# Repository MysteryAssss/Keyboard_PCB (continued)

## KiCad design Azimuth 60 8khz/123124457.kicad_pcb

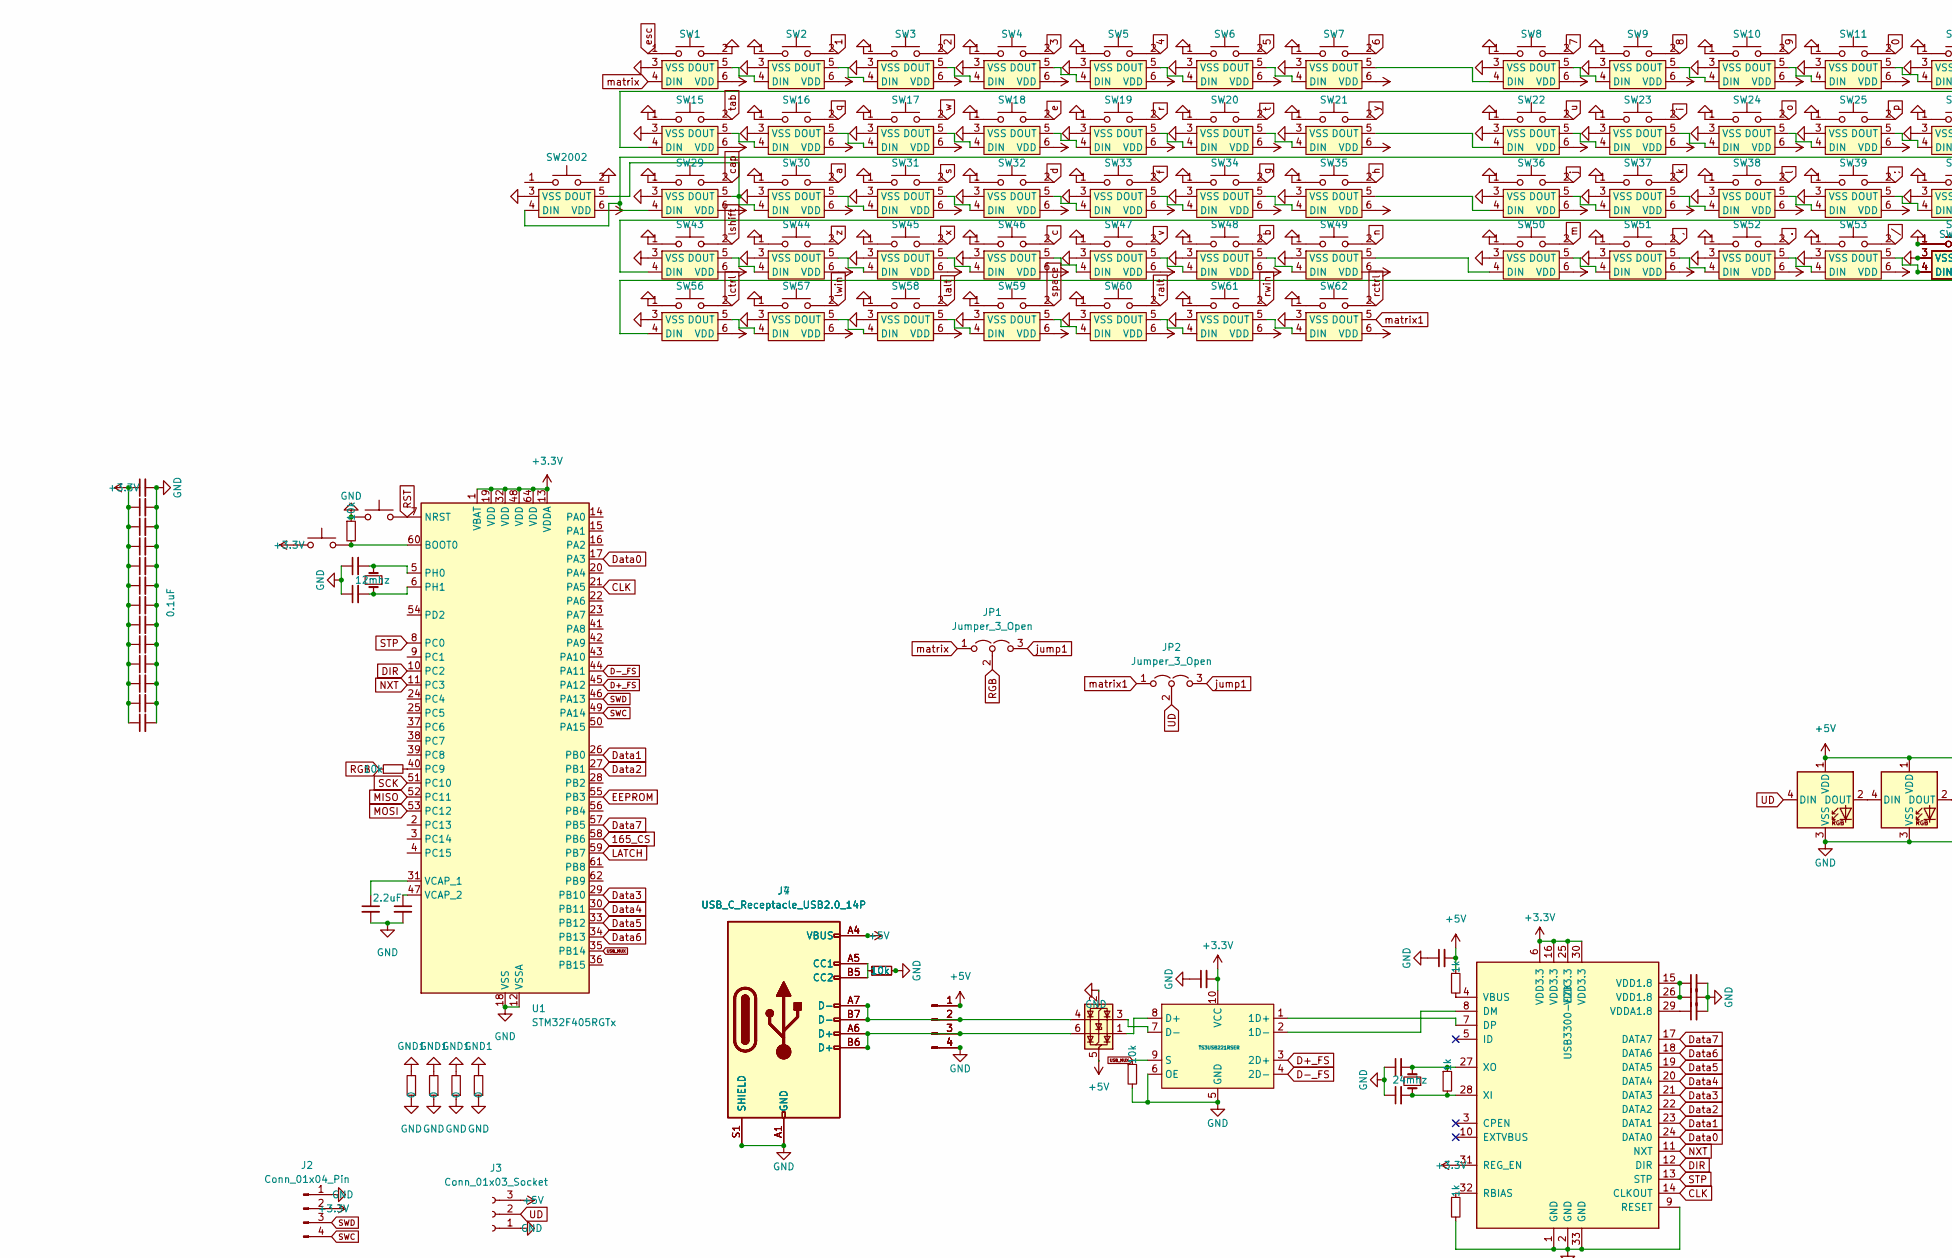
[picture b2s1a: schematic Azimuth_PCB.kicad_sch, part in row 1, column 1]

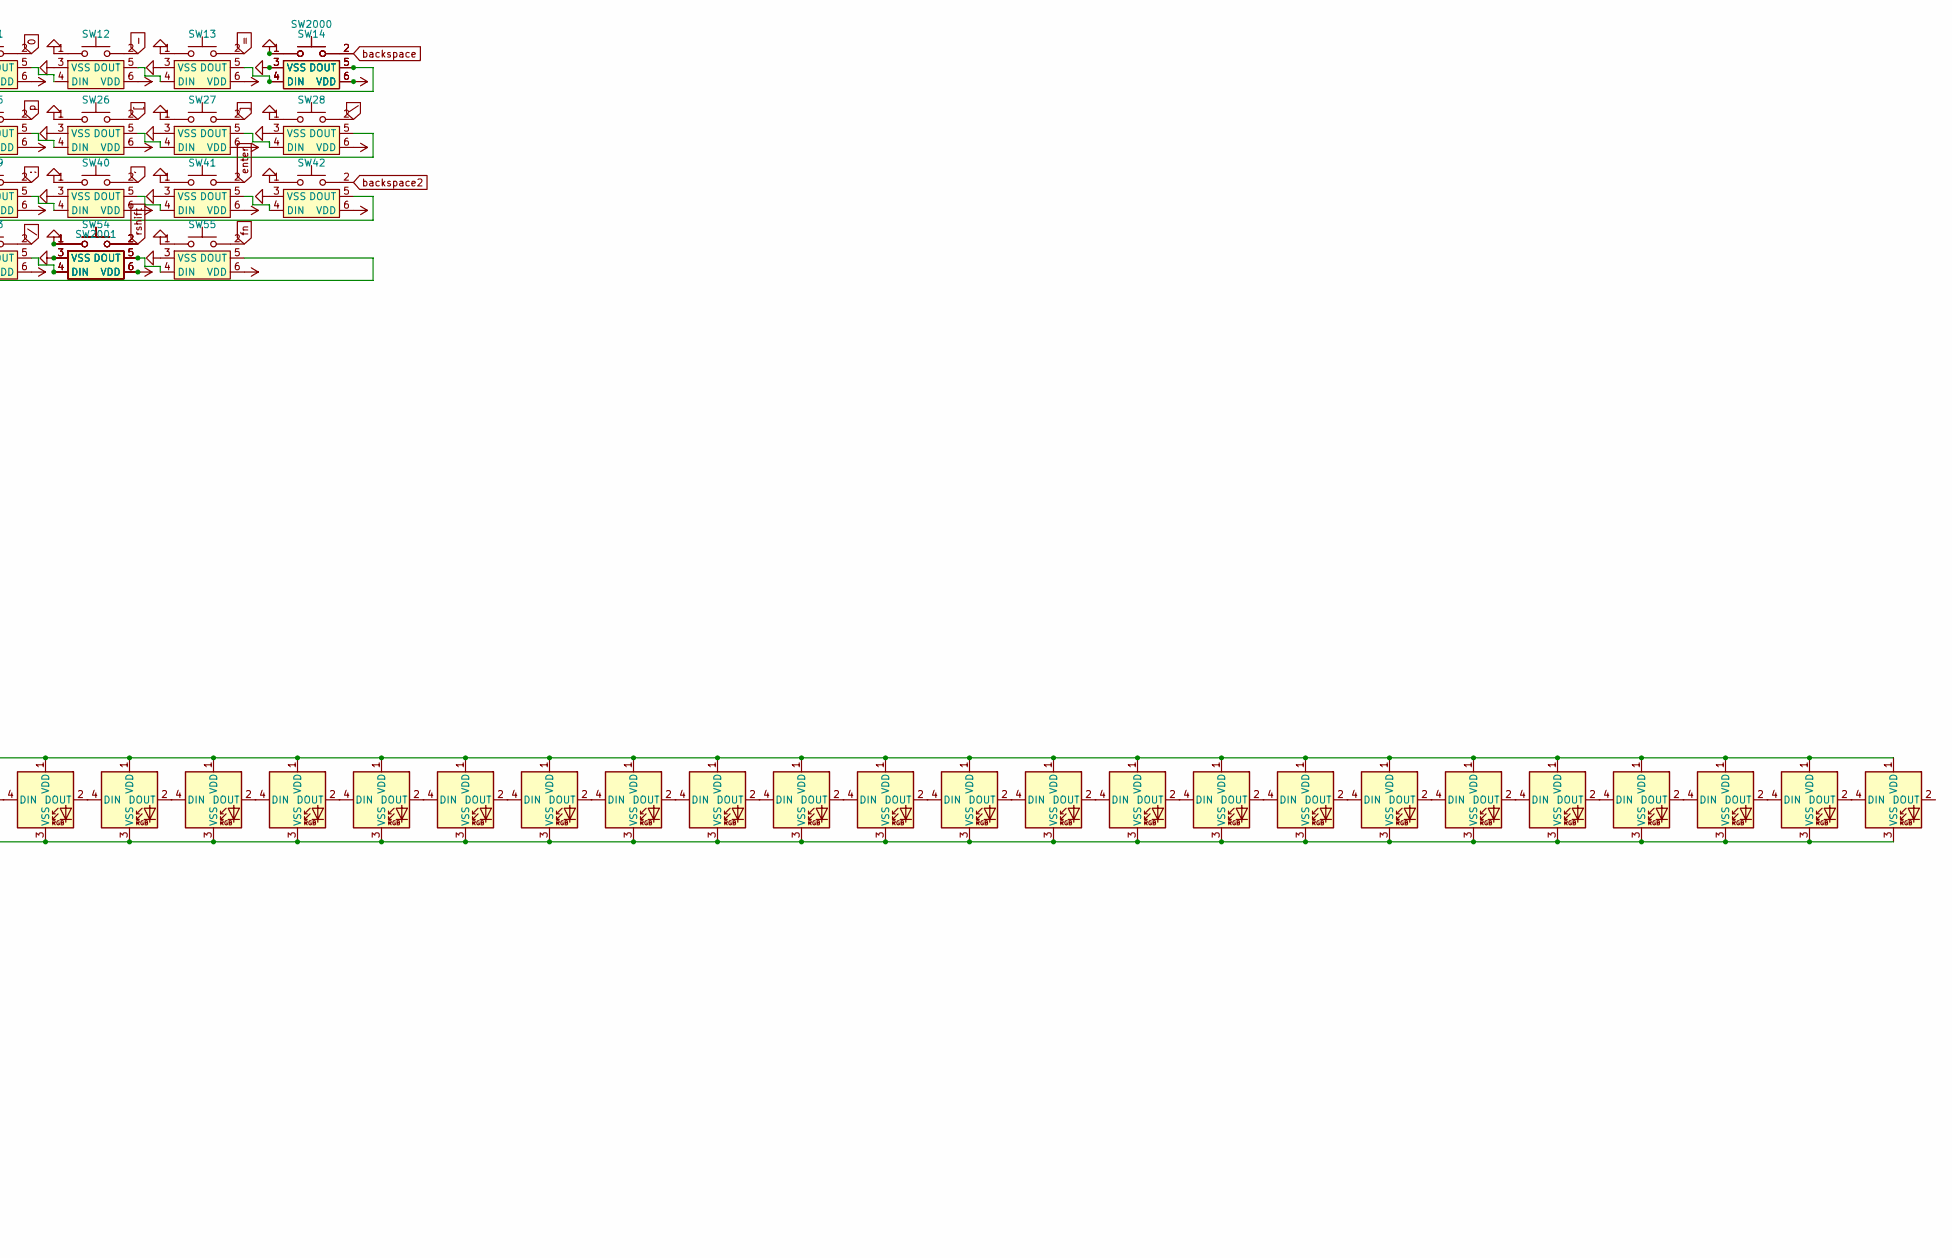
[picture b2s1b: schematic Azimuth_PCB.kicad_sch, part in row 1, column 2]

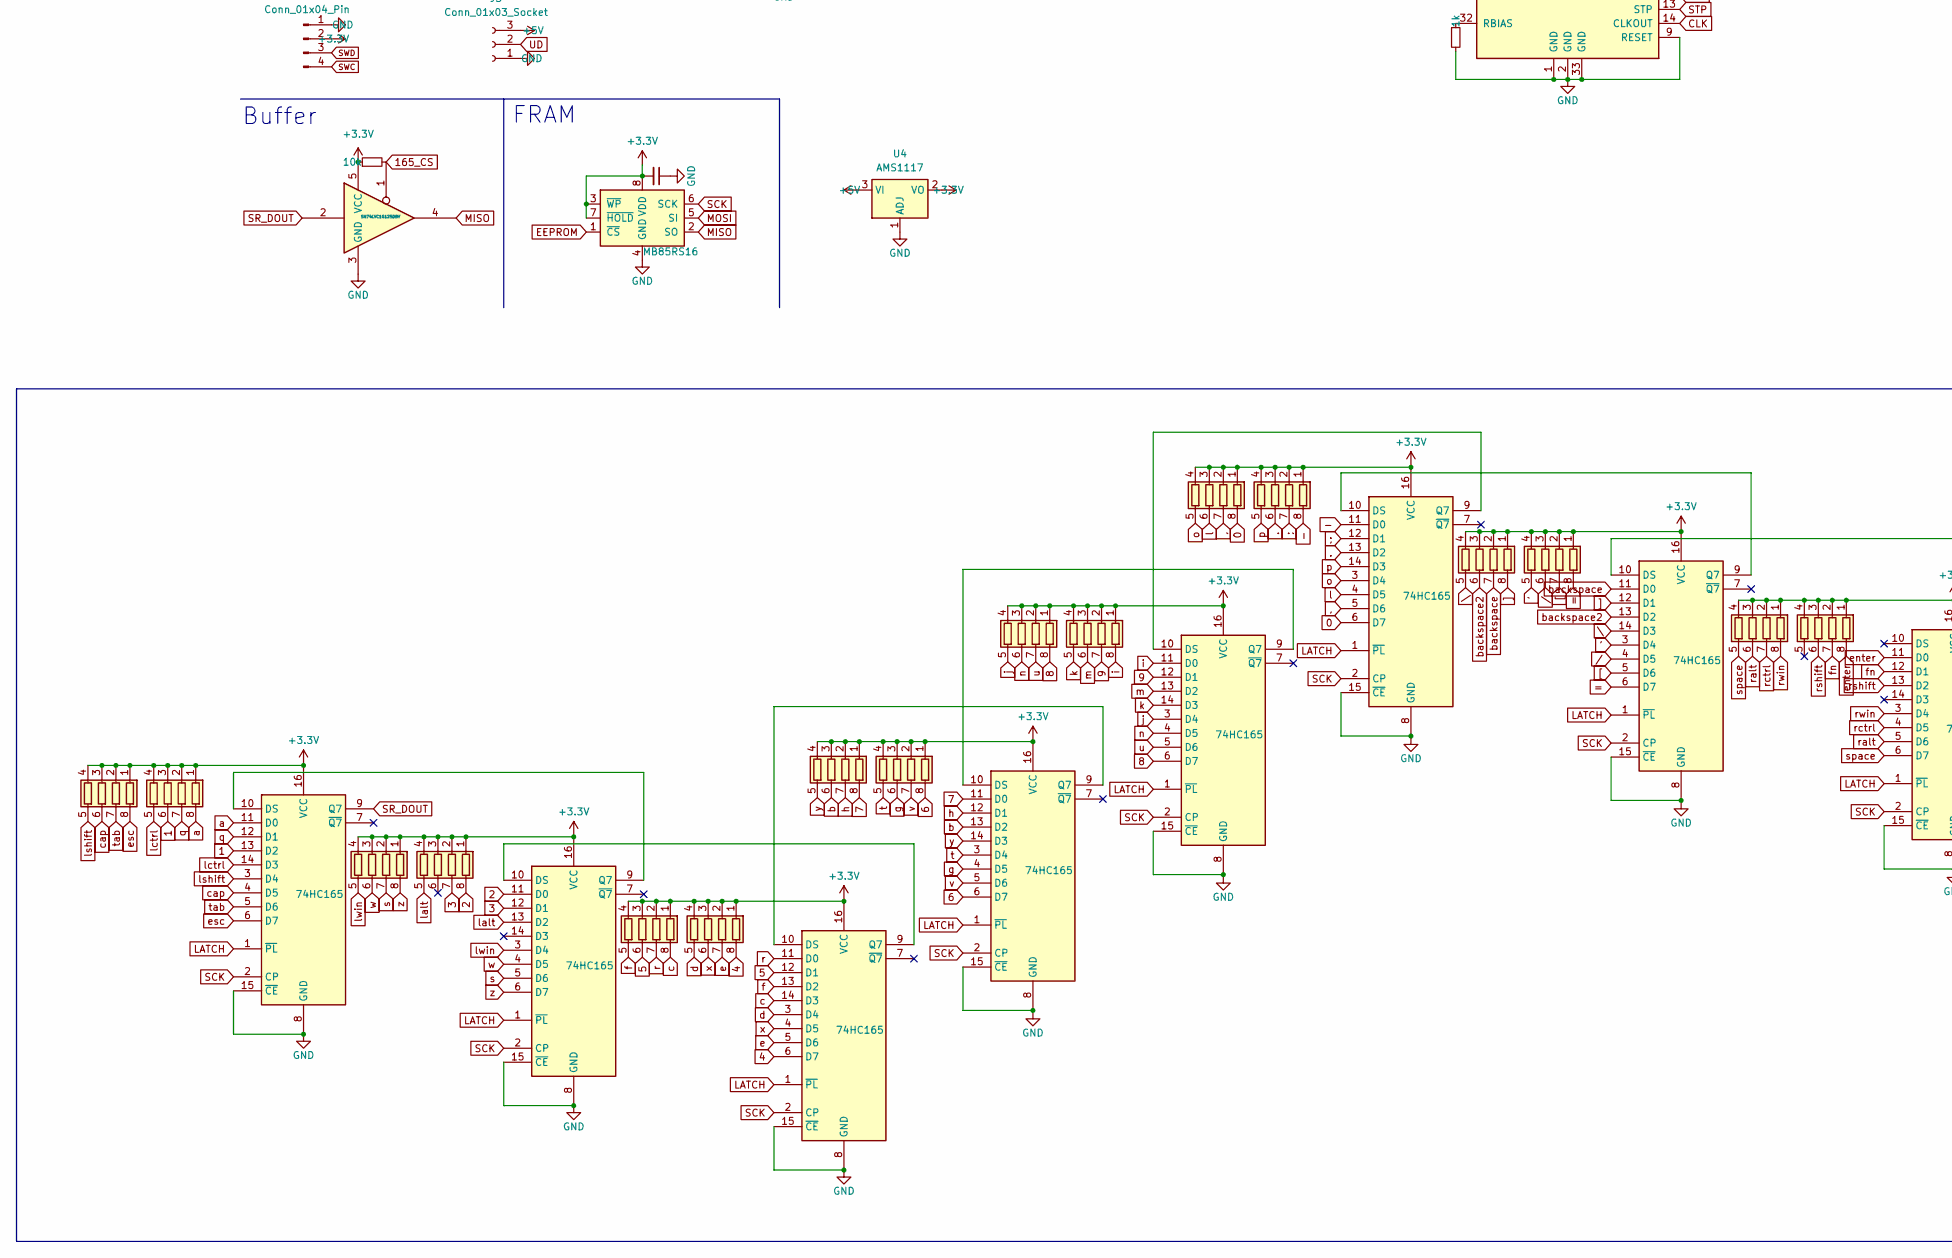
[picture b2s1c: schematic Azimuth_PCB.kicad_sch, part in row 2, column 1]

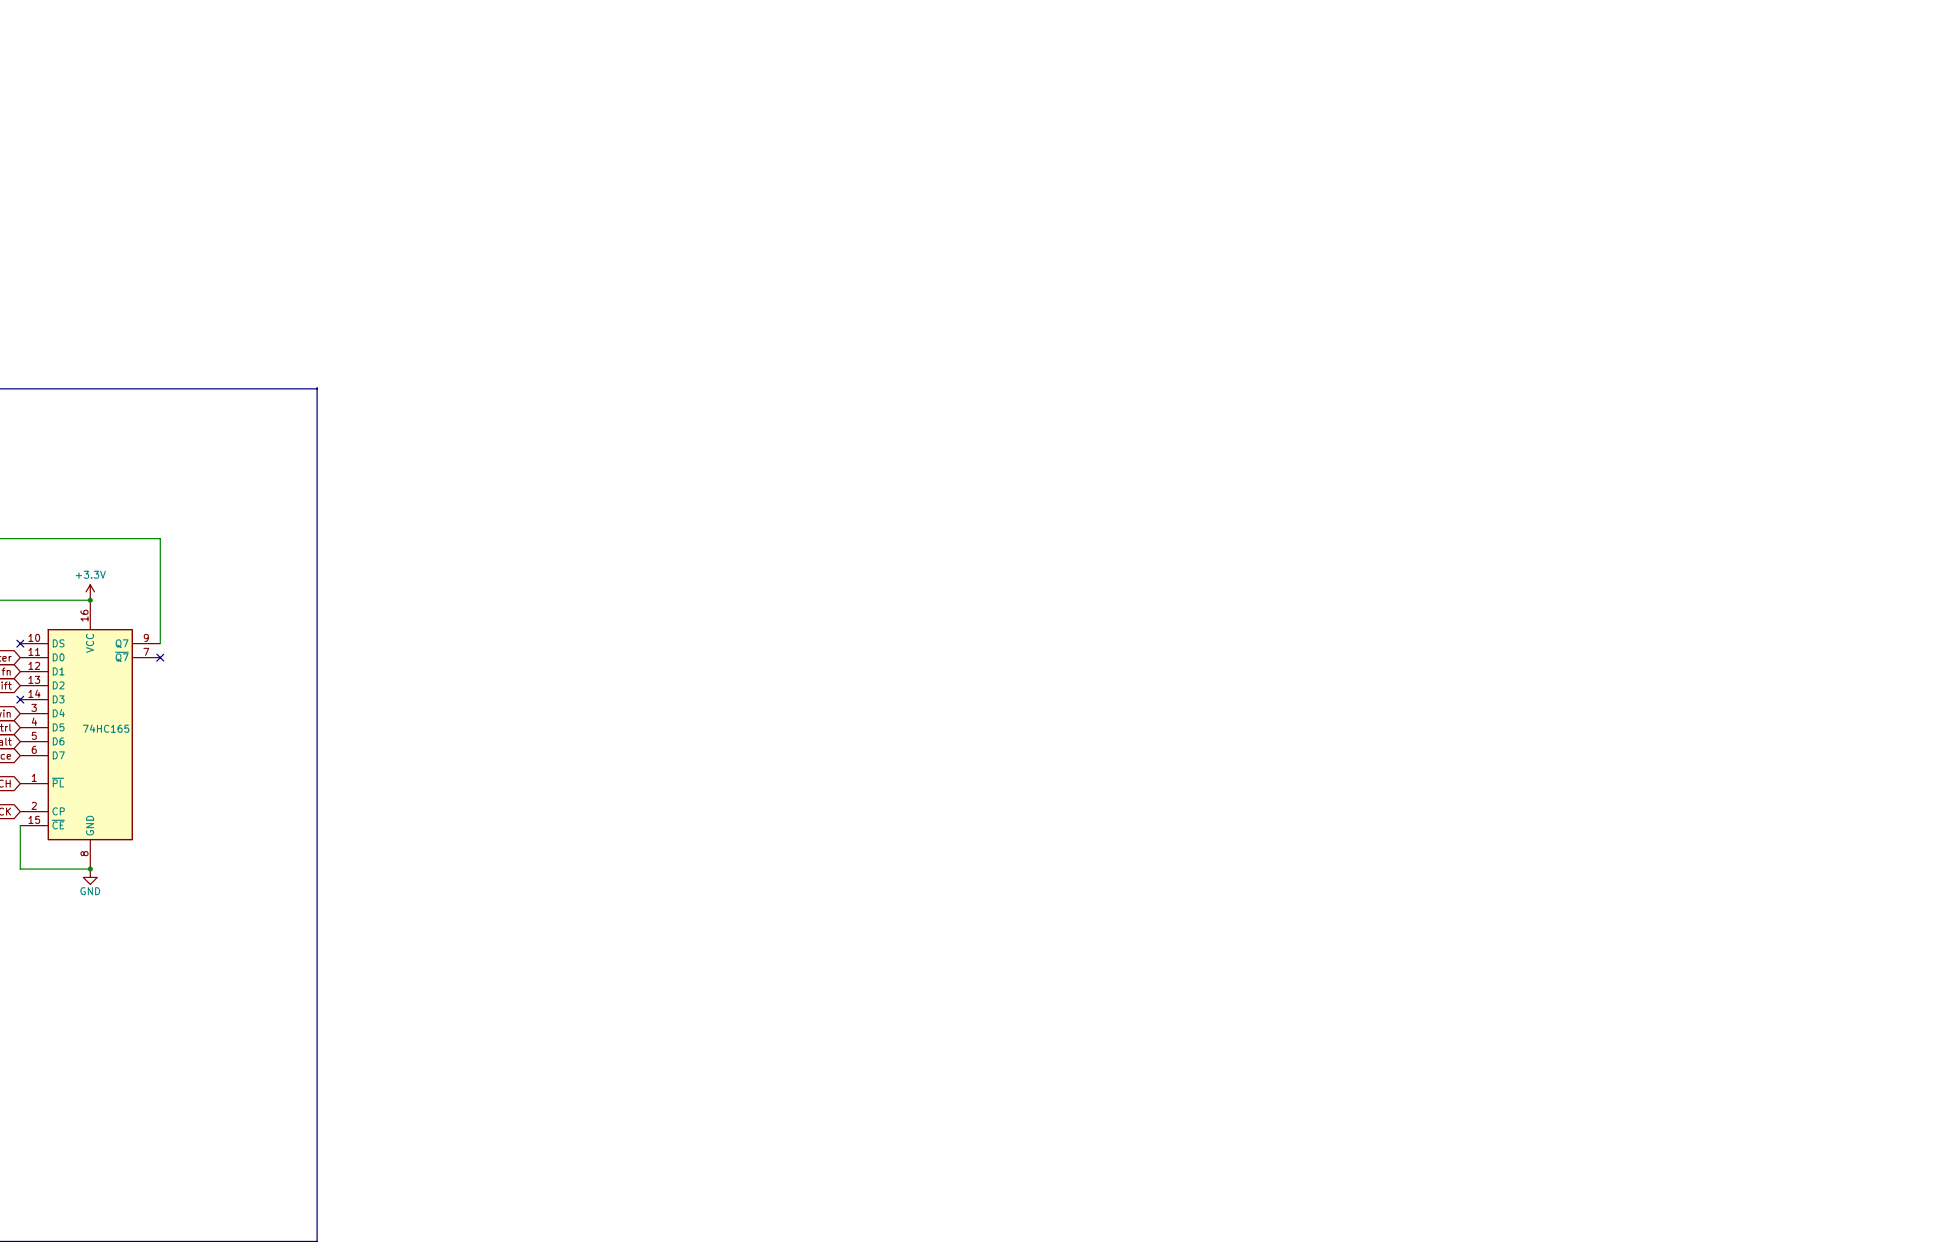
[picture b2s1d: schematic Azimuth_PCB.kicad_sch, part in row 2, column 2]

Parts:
C1, C2: 2.2uF; C_0603_1608Metric
C3, C4, C20, C21: 9pf; C_0603_1608Metric
C5, C6, C7, C8, C9, C10, C12, C14, C16: 0.1uF; C_0603_1608Metric
C11, C13, C15, C17, C18, C19, C22, C23, C24, C25: 1uF; C_0603_1608Metric
Drgb1, Drgb2, Drgb3, Drgb4, Drgb5, Drgb6, Drgb7, Drgb8, Drgb9, Drgb10, Drgb11, Drgb12, Drgb13, Drgb14, Drgb15, Drgb16, Drgb17, Drgb18, Drgb19, Drgb20, Drgb21, Drgb22, Drgb23, Drgb24: WS2812B; LED_WS2812B-2020_PLCC4_2.0x2.0mm
J1, J5, J6: Conn_01x04_Pin; JST_SH_SM04B-SRSS-TB_1x04-1MP_P1.00mm_Horizontal
J2: Conn_01x04_Pin; JST_EH_B4B-EH-A_1x04_P2.50mm_Vertical
J3: Conn_01x03_Socket; JST_SH_SM03B-SRSS-TB_1x03-1MP_P1.00mm_Horizontal
J4: USB_C_Receptacle_USB2.0_14P; USB_C_Receptacle_GCT_USB4105-xx-A_16P_TopMnt_Horizontal
J7: USB_C_Receptacle_USB2.0_14P; USB_C_Receptacle_HRO_TYPE-C-31-M-12
JP1, JP2: Jumper_3_Open; SolderJumper-3_P1.3mm_Open_RoundedPad1.0x1.5mm
R1, R2, R3, R4, R15, R20: 10k; R_0603_1608Metric
R5, R6, R7: 1k; R_0603_1608Metric
R16, R17, R18, R19: 0; R_0603_1608Metric
RN1, RN2, RN3, RN4, RN5, RN6, RN7, RN8, RN9, RN10, RN11, RN12, RN13, RN14, RN15, RN16: R_Pack04; R_Array_Convex_4x0603
SW1, SW2, SW3, SW4, SW5, SW6, SW7, SW8, SW9, SW10, SW11, SW12, SW13, SW14, SW16, SW17, SW18, SW19, SW20, SW21, SW22, SW23, SW24, SW25, SW26, SW27, SW30, SW31, SW32, SW33, SW34, SW35, SW36, SW37, SW38, SW39, SW40, SW42, SW44, SW45, SW46, SW47, SW48, SW49, SW50, SW51, SW52, SW53, SW55, SW57, SW61: CherryMX_LTST-A683CEGBW; MXOnly-1U_RGBs
SW15, SW28, SW56, SW58, SW60, SW62: CherryMX_LTST-A683CEGBW; MXOnly-1.5U_RGBs
SW29, SW54: CherryMX_LTST-A683CEGBW; MXOnly-1.75U_RGBs
SW41, SW43: CherryMX_LTST-A683CEGBW; MXOnly-2.25U_RGBs
SW59: CherryMX_LTST-A683CEGBW; MXOnly-7URGBs-ReversedStabilizers_N
SW2000: CherryMX_LTST-A683CEGBW; MXOnly-2U_RGBs
SW2001: CherryMX_LTST-A683CEGBW; MXOnly-2.75U_RGBs
SW2002: CherryMX_LTST-A683CEGBW; MXOnly-1.25U_RGBs
SWboot1, SWboot2: SW_Push; JST_XH_B2B-XH-A_1x02_P2.50mm_Vertical
U1: STM32F405RGTx; LQFP-64_10x10mm_P0.5mm
U2: SN74LVC1G125DBV; SOT-23-5
U3, U9, U10, U11, U12, U13, U14, U15: 74HC165; SOP-16_3.9x9.9mm_P1.27mm
U4: AMS1117; SOT-223-3_TabPin2
U5: TS3USB221RSER; UQFN-10
U6: USBLC6-2SC6; SOT-23-6
U7: USB3300-EZK; QFN-32-1EP_5x5mm_P0.5mm_EP3.45x3.45mm
U8: MB85RS16; SOIC-8_3.9x4.9mm_P1.27mm
Y1: 12mhz; Crystal_SMD_5032-2Pin_5.0x3.2mm
Y3: 24mhz; Crystal_SMD_5032-2Pin_5.0x3.2mm

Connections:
0: RN11.8 (R1.2), SW11.2, U14.6 (D7)
1: RN1.6 (R3.2), SW2.2, U3.13 (D2)
2: RN4.8 (R1.2), SW3.2, U9.11 (D0)
3: RN4.7 (R2.2), SW4.2, U9.12 (D1)
4: RN6.8 (R1.2), SW5.2, U10.6 (D7)
5: RN5.6 (R3.2), SW6.2, U10.12 (D1)
6: RN8.8 (R1.2), SW7.2, U11.6 (D7)
7: RN7.8 (R1.2), SW8.2, U11.11 (D0)
8: RN9.8 (R1.2), SW9.2, U12.6 (D7)
9: RN10.7 (R2.2), SW10.2, U12.12 (D1)
165_CS: R2.2, U1.58 (PB6), U2.1
': RN14.5 (R4.2), SW40.2, U15.3 (D4)
+3.3V: C5.1, C6.1, C7.1, C8.1, C9.1, C10.1, C11.1, C12.1, C13.1, C14.1, C15.1, C16.1, C17.1, C18.2, C25.2, J2.2, R2.1, RN1.1 (R1.1), RN1.2 (R2.1), RN1.3 (R3.1), RN1.4 (R4.1), RN2.1 (R1.1), RN2.2 (R2.1), RN2.3 (R3.1), RN2.4 (R4.1), RN3.1 (R1.1), RN3.2 (R2.1), RN3.3 (R3.1), RN3.4 (R4.1), RN4.1 (R1.1), RN4.2 (R2.1), RN4.3 (R3.1), RN4.4 (R4.1), RN5.1 (R1.1), RN5.2 (R2.1), RN5.3 (R3.1), RN5.4 (R4.1), RN6.1 (R1.1), RN6.2 (R2.1), RN6.3 (R3.1), RN6.4 (R4.1), RN7.1 (R1.1), RN7.2 (R2.1), RN7.3 (R3.1), RN7.4 (R4.1), RN8.1 (R1.1), RN8.2 (R2.1), RN8.3 (R3.1), RN8.4 (R4.1), RN9.1 (R1.1), RN9.2 (R2.1), RN9.3 (R3.1), RN9.4 (R4.1), RN10.1 (R1.1), RN10.2 (R2.1), RN10.3 (R3.1), RN10.4 (R4.1), RN11.1 (R1.1), RN11.2 (R2.1), RN11.3 (R3.1), RN11.4 (R4.1), RN12.1 (R1.1), RN12.2 (R2.1), RN12.3 (R3.1), RN12.4 (R4.1), RN13.1 (R1.1), RN13.2 (R2.1), RN13.3 (R3.1), RN13.4 (R4.1), RN14.1 (R1.1), RN14.2 (R2.1), RN14.3 (R3.1), RN14.4 (R4.1), RN15.1 (R1.1), RN15.2 (R2.1), RN15.3 (R3.1), RN15.4 (R4.1), RN16.1 (R1.1), RN16.2 (R2.1), RN16.3 (R3.1), RN16.4 (R4.1), SWboot2.1, U1.1 (VBAT), U1.13 (VDDA), U1.19 (VDD), U1.32 (VDD), U1.48 (VDD), U1.64 (VDD), U2.5 (VCC), U3.16 (VCC), U4.2 (VO), U5.10 (VCC), U7.6 (VDD3.3), U7.16 (VDD3.3), U7.25 (VDD3.3), U7.30 (VDD3.3), U7.31 (REG_EN), U8.3 (~WP), U8.7 (~HOLD), U8.8 (VDD), U9.16 (VCC), U10.16 (VCC), U11.16 (VCC), U12.16 (VCC), U13.16 (VCC), U14.16 (VCC), U15.16 (VCC)
,: RN11.7 (R2.2), SW51.2, U14.5 (D6)
-: RN12.8 (R1.2), SW12.2, U14.11 (D0)
.: RN12.6 (R3.2), SW52.2, U14.13 (D2)
;: RN12.7 (R2.2), SW39.2, U14.12 (D1)
=: RN14.8 (R1.2), SW13.2, U15.6 (D7)
CLK: U1.21 (PA5), U7.14 (CLKOUT)
D+_FS: U1.45 (PA12), U5.3 (2D+)
D-_FS: U1.44 (PA11), U5.4 (2D-)
DIR: U1.10 (PC2), U7.12 (DIR)
Data0: U1.17 (PA3), U7.24 (DATA0)
Data1: U1.26 (PB0), U7.23 (DATA1)
Data2: U1.27 (PB1), U7.22 (DATA2)
Data3: U1.29 (PB10), U7.21 (DATA3)
Data4: U1.30 (PB11), U7.20 (DATA4)
Data5: U1.33 (PB12), U7.19 (DATA5)
Data6: U1.34 (PB13), U7.18 (DATA6)
Data7: U1.57 (PB5), U7.17 (DATA7)
EEPROM: U1.55 (PB3), U8.1 (~CS)
GND: C1.2, C2.2, C3.1, C4.1, C5.2, C6.2, C7.2, C8.2, C9.2, C10.2, C11.2, C12.2, C13.2, C14.2, C15.2, C16.2, C17.2, C18.1, C19.1, C20.1, C21.1, C22.2, C23.2, C24.2, C25.1, Drgb1.3 (VSS), Drgb2.3 (VSS), Drgb3.3 (VSS), Drgb4.3 (VSS), Drgb5.3 (VSS), Drgb6.3 (VSS), Drgb7.3 (VSS), Drgb8.3 (VSS), Drgb9.3 (VSS), Drgb10.3 (VSS), Drgb11.3 (VSS), Drgb12.3 (VSS), Drgb13.3 (VSS), Drgb14.3 (VSS), Drgb15.3 (VSS), Drgb16.3 (VSS), Drgb17.3 (VSS), Drgb18.3 (VSS), Drgb19.3 (VSS), Drgb20.3 (VSS), Drgb21.3 (VSS), Drgb22.3 (VSS), Drgb23.3 (VSS), Drgb24.3 (VSS), J1.4, J2.1, J3.1, J4.A1 (GND), J4.A12 (GND), J4.B1 (GND), J4.B12 (GND), J4.S1 (SHIELD), J5.4, J6.4, J7.A1 (GND), J7.A12 (GND), J7.B1 (GND), J7.B12 (GND), J7.S1 (SHIELD), R1.1, R3.2, R4.2, R7.2, R16.1, R17.1, R18.1, R19.1, R20.2, SW1.3 (VSS), SW2.3 (VSS), SW3.3 (VSS), SW4.3 (VSS), SW5.3 (VSS), SW6.3 (VSS), SW7.3 (VSS), SW8.3 (VSS), SW9.3 (VSS), SW10.3 (VSS), SW11.3 (VSS), SW12.3 (VSS), SW13.3 (VSS), SW14.3 (VSS), SW15.3 (VSS), SW16.3 (VSS), SW17.3 (VSS), SW18.3 (VSS), SW19.3 (VSS), SW20.3 (VSS), SW21.3 (VSS), SW22.3 (VSS), SW23.3 (VSS), SW24.3 (VSS), SW25.3 (VSS), SW26.3 (VSS), SW27.3 (VSS), SW28.3 (VSS), SW29.3 (VSS), SW30.3 (VSS), SW31.3 (VSS), SW32.3 (VSS), SW33.3 (VSS), SW34.3 (VSS), SW35.3 (VSS), SW36.3 (VSS), SW37.3 (VSS), SW38.3 (VSS), SW39.3 (VSS), SW40.3 (VSS), SW41.3 (VSS), SW42.3 (VSS), SW43.3 (VSS), SW44.3 (VSS), SW45.3 (VSS), SW46.3 (VSS), SW47.3 (VSS), SW48.3 (VSS), SW49.3 (VSS), SW50.3 (VSS), SW51.3 (VSS), SW52.3 (VSS), SW53.3 (VSS), SW54.3 (VSS), SW55.3 (VSS), SW56.3 (VSS), SW57.3 (VSS), SW58.3 (VSS), SW59.3 (VSS), SW60.3 (VSS), SW61.3 (VSS), SW62.3 (VSS), SW2000.3 (VSS), SW2001.3 (VSS), SW2002.3 (VSS), SWboot1.1, U1.12 (VSSA), U1.18 (VSS), U1.63 (VSS), U2.3 (GND), U3.8 (GND), U3.15 (~CE), U4.1 (ADJ), U5.5 (GND), U5.6 (OE), U6.2 (GND), U7.1 (GND), U7.2 (GND), U7.9 (RESET), U7.33 (GND), U8.4 (GND), U9.8 (GND), U9.15 (~CE), U10.8 (GND), U10.15 (~CE), U11.8 (GND), U11.15 (~CE), U12.8 (GND), U12.15 (~CE), U13.8 (GND), U13.15 (~CE), U14.8 (GND), U14.15 (~CE), U15.8 (GND), U15.15 (~CE); also elsewhere on the board
GND1: R16.2, R17.2, R18.2, R19.2, SW1.2, SW2.1, SW3.1, SW4.1, SW5.1, SW6.1, SW7.1, SW8.1, SW9.1, SW10.1, SW11.1, SW12.1, SW13.1, SW14.1, SW15.1, SW16.1, SW17.1, SW18.1, SW19.1, SW20.1, SW21.1, SW22.1, SW23.1, SW24.1, SW25.1, SW26.1, SW27.1, SW28.1, SW29.1, SW30.1, SW31.1, SW32.1, SW33.1, SW34.1, SW35.1, SW36.1, SW37.1, SW38.1, SW39.1, SW40.1, SW41.1, SW42.1, SW43.1, SW44.1, SW45.1, SW46.1, SW47.1, SW48.1, SW49.1, SW50.1, SW51.1, SW52.1, SW53.1, SW54.1, SW55.1, SW56.1, SW57.1, SW58.1, SW59.1, SW60.1, SW61.1, SW62.1, SW2000.1, SW2001.1, SW2002.2
LATCH: U1.59 (PB7), U3.1 (~PL), U9.1 (~PL), U10.1 (~PL), U11.1 (~PL), U12.1 (~PL), U13.1 (~PL), U14.1 (~PL), U15.1 (~PL)
MISO: U1.52 (PC11), U2.4, U8.2 (SO)
MOSI: U1.53 (PC12), U8.5 (SI)
NXT: U1.11 (PC3), U7.11 (NXT)
unnamed: C22.1, C23.1, U7.15 (VDD1.8), U7.26 (VDD1.8)
unnamed: Drgb1.4 (DIN), Drgb16.2 (DOUT)
unnamed: Drgb1.2 (DOUT), Drgb2.4 (DIN)
unnamed: Drgb2.2 (DOUT), Drgb3.4 (DIN)
unnamed: Drgb3.2 (DOUT), Drgb4.4 (DIN)
unnamed: Drgb4.2 (DOUT), Drgb5.4 (DIN)
unnamed: Drgb5.2 (DOUT), Drgb6.4 (DIN)
unnamed: Drgb6.2 (DOUT), Drgb7.4 (DIN)
unnamed: Drgb7.2 (DOUT), Drgb8.4 (DIN)
unnamed: Drgb8.2 (DOUT), Drgb9.4 (DIN)
unnamed: Drgb9.2 (DOUT), Drgb10.4 (DIN)
unnamed: Drgb10.2 (DOUT), Drgb11.4 (DIN)
unnamed: Drgb11.2 (DOUT), Drgb12.4 (DIN)
unnamed: Drgb12.2 (DOUT), Drgb13.4 (DIN)
unnamed: Drgb13.2 (DOUT), Drgb14.4 (DIN)
unnamed: Drgb14.2 (DOUT), Drgb15.4 (DIN)
unnamed: Drgb15.2 (DOUT), Drgb17.4 (DIN)
unnamed: Drgb17.2 (DOUT), Drgb18.4 (DIN)
unnamed: Drgb18.2 (DOUT), Drgb19.4 (DIN)
unnamed: Drgb19.2 (DOUT), Drgb20.4 (DIN)
unnamed: Drgb20.2 (DOUT), Drgb21.4 (DIN)
unnamed: Drgb21.2 (DOUT), Drgb22.4 (DIN)
unnamed: Drgb22.2 (DOUT), Drgb23.4 (DIN)
unnamed: Drgb23.2 (DOUT), Drgb24.4 (DIN)
unnamed 61: J1.2, J4.A7 (D-), J4.B7 (D-), J5.2, J6.2, J7.A7 (D-), J7.B7 (D-), U6.4 (I/O2); also elsewhere on the board
unnamed 62: J1.3, J4.A6 (D+), J4.B6 (D+), J5.3, J6.3, J7.A6 (D+), J7.B6 (D+), U6.6 (I/O1); also elsewhere on the board
unnamed: SW1.5 (DOUT), SW2.4 (DIN)
unnamed: SW2.5 (DOUT), SW3.4 (DIN)
unnamed: SW3.5 (DOUT), SW4.4 (DIN)
unnamed: SW4.5 (DOUT), SW5.4 (DIN)
unnamed: SW5.5 (DOUT), SW6.4 (DIN)
unnamed: SW6.5 (DOUT), SW7.4 (DIN)
unnamed: SW7.5 (DOUT), SW8.4 (DIN)
unnamed: SW8.5 (DOUT), SW9.4 (DIN)
unnamed: SW9.5 (DOUT), SW10.4 (DIN)
unnamed: SW10.5 (DOUT), SW11.4 (DIN)
unnamed: SW11.5 (DOUT), SW12.4 (DIN)
unnamed: SW12.5 (DOUT), SW13.4 (DIN)
unnamed: SW13.5 (DOUT), SW14.4 (DIN), SW2000.4 (DIN)
unnamed: SW14.5 (DOUT), SW15.4 (DIN), SW2000.5 (DOUT)
unnamed: SW15.5 (DOUT), SW16.4 (DIN)
unnamed: SW16.5 (DOUT), SW17.4 (DIN)
unnamed: SW17.5 (DOUT), SW18.4 (DIN)
unnamed: SW18.5 (DOUT), SW19.4 (DIN)
unnamed: SW19.5 (DOUT), SW20.4 (DIN)
unnamed: SW20.5 (DOUT), SW21.4 (DIN)
unnamed: SW21.5 (DOUT), SW22.4 (DIN)
unnamed: SW22.5 (DOUT), SW23.4 (DIN)
unnamed: SW23.5 (DOUT), SW24.4 (DIN)
unnamed: SW24.5 (DOUT), SW25.4 (DIN)
unnamed: SW25.5 (DOUT), SW26.4 (DIN)
unnamed: SW26.5 (DOUT), SW27.4 (DIN)
unnamed: SW27.5 (DOUT), SW28.4 (DIN)
unnamed: SW30.5 (DOUT), SW31.4 (DIN)
unnamed: SW31.5 (DOUT), SW32.4 (DIN)
unnamed: SW32.5 (DOUT), SW33.4 (DIN)
unnamed: SW33.5 (DOUT), SW34.4 (DIN)
unnamed: SW34.5 (DOUT), SW35.4 (DIN)
unnamed: SW35.5 (DOUT), SW36.4 (DIN)
unnamed: SW36.5 (DOUT), SW37.4 (DIN)
unnamed: SW37.5 (DOUT), SW38.4 (DIN)
unnamed: SW38.5 (DOUT), SW39.4 (DIN)
unnamed: SW39.5 (DOUT), SW40.4 (DIN)
unnamed: SW40.5 (DOUT), SW41.4 (DIN)
unnamed: SW41.5 (DOUT), SW42.4 (DIN)
unnamed: SW42.5 (DOUT), SW43.4 (DIN)
unnamed: SW43.5 (DOUT), SW44.4 (DIN)
unnamed: SW44.5 (DOUT), SW45.4 (DIN)
unnamed: SW45.5 (DOUT), SW46.4 (DIN)
unnamed: SW46.5 (DOUT), SW47.4 (DIN)
unnamed: SW47.5 (DOUT), SW48.4 (DIN)
unnamed: SW48.5 (DOUT), SW49.4 (DIN)
unnamed: SW49.5 (DOUT), SW50.4 (DIN)
unnamed: SW50.5 (DOUT), SW51.4 (DIN)
unnamed: SW51.5 (DOUT), SW52.4 (DIN)
unnamed: SW52.5 (DOUT), SW53.4 (DIN)
unnamed: SW55.5 (DOUT), SW56.4 (DIN)
unnamed: SW56.5 (DOUT), SW57.4 (DIN)
unnamed: SW57.5 (DOUT), SW58.4 (DIN)
unnamed: SW58.5 (DOUT), SW59.4 (DIN)
unnamed: SW59.5 (DOUT), SW60.4 (DIN)
unnamed: SW60.5 (DOUT), SW61.4 (DIN)
unnamed: SW61.5 (DOUT), SW62.4 (DIN)
unnamed: SW53.5 (DOUT), SW54.4 (DIN), SW2001.4 (DIN)
unnamed: SW54.5 (DOUT), SW55.4 (DIN), SW2001.5 (DOUT)
unnamed: SW29.5 (DOUT), SW30.4 (DIN), SW2002.5 (DOUT)
unnamed: R1.2, SWboot2.2, U1.60 (BOOT0)
unnamed: R15.2, U1.40 (PC9)
unnamed: C3.2, U1.5 (PH0), Y1.2
unnamed: C4.2, U1.6 (PH1), Y1.1
unnamed: C2.1, U1.31 (VCAP_1)
unnamed: C1.1, U1.47 (VCAP_2)
unnamed: U3.10 (DS), U9.9 (Q7)
unnamed: U5.1 (1D+), U7.7 (DP)
unnamed: U5.2 (1D-), U7.8 (DM)
unnamed: U5.8 (D+), U6.1 (I/O1)
unnamed: U5.7 (D-), U6.3 (I/O2)
unnamed: R7.1, U7.32 (RBIAS)
unnamed: R5.2, U7.4 (VBUS)
unnamed: C24.1, U7.29 (VDDA1.8)
unnamed: C21.2, R6.2, U7.28 (XI), Y3.1
unnamed: C20.2, R6.1, U7.27 (XO), Y3.2
unnamed: U10.10 (DS), U11.9 (Q7)
unnamed: U9.10 (DS), U10.9 (Q7)
unnamed: U11.10 (DS), U12.9 (Q7)
unnamed: U12.10 (DS), U14.9 (Q7)
unnamed: U13.9 (Q7), U15.10 (DS)
unnamed: U14.10 (DS), U15.9 (Q7)
RGB: JP1.2 (C), R15.1
RST: SWboot1.2, U1.7 (NRST)
SCK: U1.51 (PC10), U3.2 (CP), U8.6 (SCK), U9.2 (CP), U10.2 (CP), U11.2 (CP), U12.2 (CP), U13.2 (CP), U14.2 (CP), U15.2 (CP)
SR_DOUT: U2.2, U3.9 (Q7)
STP: U1.8 (PC0), U7.13 (STP)
SWC: J2.4, U1.49 (PA14)
SWD: J2.3, U1.46 (PA13)
UD: Drgb16.4 (DIN), J3.2, JP2.2 (C)
USB_MUX: R4.1, U1.35 (PB14), U5.9 (S)
[: RN14.7 (R2.2), SW26.2, U15.5 (D6)
\: RN13.5 (R4.2), SW28.2, U15.14 (D3)
]: RN13.8 (R1.2), SW27.2, U15.12 (D1)
a: RN1.8 (R1.2), SW30.2, U3.11 (D0)
b: RN7.6 (R3.2), SW48.2, U11.13 (D2)
backspace: RN13.7 (R2.2), SW14.2, SW2000.2, U15.11 (D0)
backspace2: RN13.6 (R3.2), SW42.2, U15.13 (D2)
c: RN5.8 (R1.2), SW46.2, U10.14 (D3)
cap: RN2.6 (R3.2), SW29.2, U3.4 (D5)
d: RN6.5 (R4.2), SW32.2, U10.3 (D4)
e: RN6.7 (R2.2), SW18.2, U10.5 (D6)
enter: RN16.8 (R1.2), SW41.2, U13.11 (D0)
esc: RN2.8 (R1.2), SW1.1, U3.6 (D7)
f: RN5.5 (R4.2), SW33.2, U10.13 (D2)
fn: RN16.7 (R2.2), SW55.2, U13.12 (D1)
g: RN8.6 (R3.2), SW34.2, U11.4 (D5)
h: RN7.7 (R2.2), SW35.2, U11.12 (D1)
i: RN10.8 (R1.2), SW23.2, U12.11 (D0)
j: RN9.5 (R4.2), SW36.2, U12.3 (D4)
jump1: JP1.3 (B), JP2.3 (B)
k: RN10.5 (R4.2), SW37.2, U12.14 (D3)
l: RN11.6 (R3.2), SW38.2, U14.4 (D5)
lalt: RN4.5 (R4.2), SW58.2, U9.13 (D2)
lctrl: RN1.5 (R4.2), SW56.2, U3.14 (D3)
lshift: RN2.5 (R4.2), SW43.2, U3.3 (D4)
lwin: RN3.5 (R4.2), SW57.2, U9.3 (D4)
m: RN10.6 (R3.2), SW50.2, U12.13 (D2)
matrix: JP1.1 (A), SW1.4 (DIN)
matrix1: JP2.1 (A), SW62.5 (DOUT)
n: RN9.6 (R3.2), SW49.2, U12.4 (D5)
o: RN11.5 (R4.2), SW24.2, U14.3 (D4)
p: RN12.5 (R4.2), SW25.2, U14.14 (D3)
q: RN1.7 (R2.2), SW16.2, U3.12 (D1)
r: RN5.7 (R2.2), SW19.2, U10.11 (D0)
ralt: RN15.6 (R3.2), SW60.2, U13.5 (D6)
rctrl: RN15.7 (R2.2), SW62.2, U13.4 (D5)
rshift: RN16.6 (R3.2), SW54.2, SW2001.2, U13.13 (D2)
rwin: RN15.8 (R1.2), SW61.2, U13.3 (D4)
s: RN3.7 (R2.2), SW31.2, U9.5 (D6)
space: RN15.5 (R4.2), SW59.2, U13.6 (D7)
t: RN8.5 (R4.2), SW20.2, U11.3 (D4)
tab: RN2.7 (R2.2), SW15.2, U3.5 (D6)
u: RN9.7 (R2.2), SW22.2, U12.5 (D6)
v: RN8.7 (R2.2), SW47.2, U11.5 (D6)
w: RN3.6 (R3.2), SW17.2, U9.4 (D5)
x: RN6.6 (R3.2), SW45.2, U10.4 (D5)
y: RN7.5 (R4.2), SW21.2, U11.14 (D3)
z: RN3.8 (R1.2), SW44.2, U9.6 (D7)
/: RN14.6 (R3.2), SW53.2, U15.4 (D5)

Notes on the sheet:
FRAM
Buffer

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
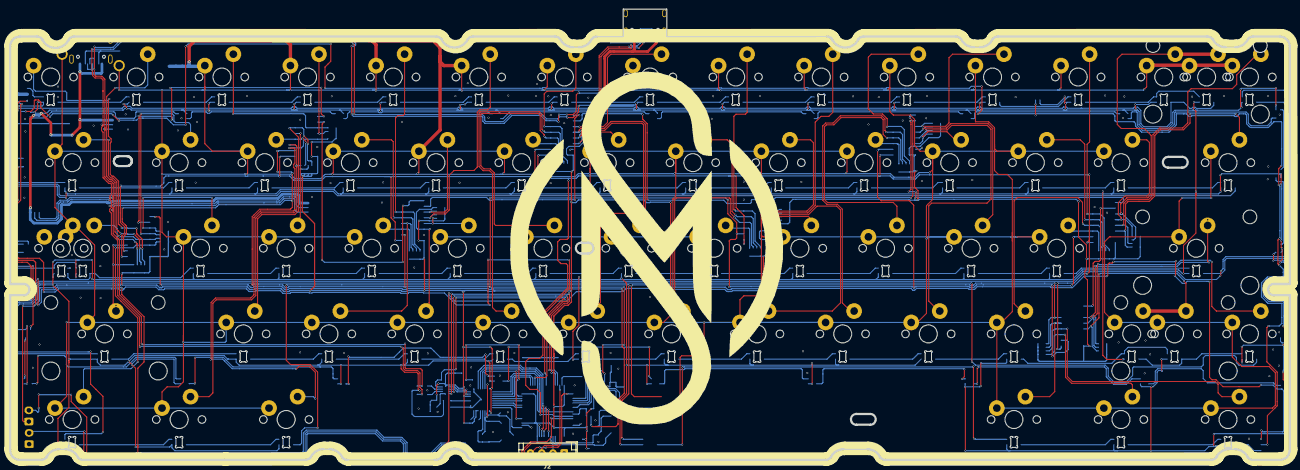
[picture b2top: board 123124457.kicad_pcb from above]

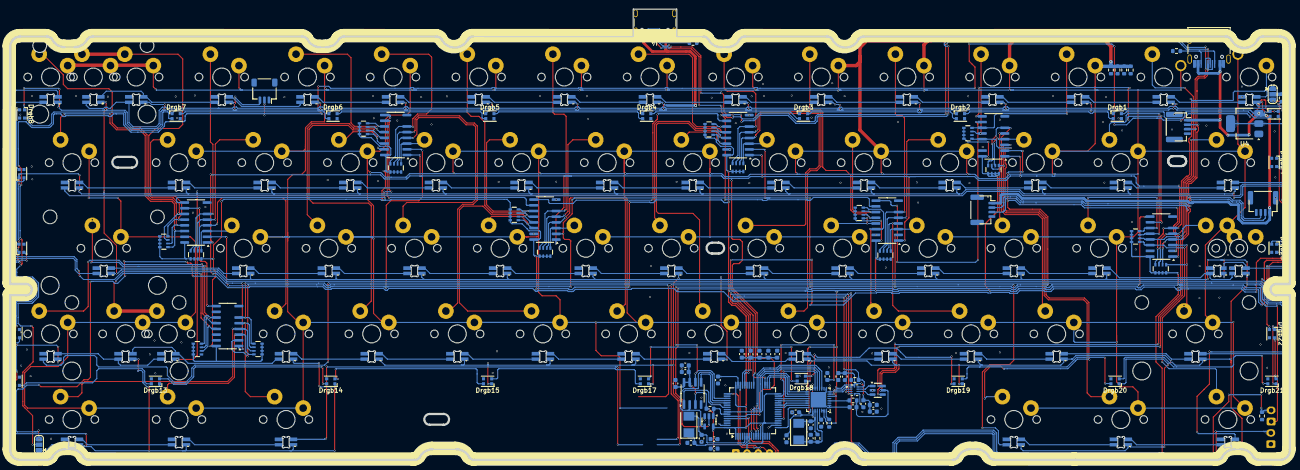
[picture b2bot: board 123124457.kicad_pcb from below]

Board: 11 copper layers, 284.7 x 100.3 mm, 170 parts (103 on the bottom side), 204 nets.

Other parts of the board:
J4#2: USB_C_Receptacle_USB2.0_14P; USB_C_Receptacle_HRO_TYPE-C-31-M-12

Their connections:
GND: J4#2.A1 (GND), J4#2.A12 (GND), J4#2.B1 (GND), J4#2.B12 (GND), J4#2.S1 (SHIELD); also elsewhere on the board
unnamed 61: J4#2.A7 (D-), J4#2.B7 (D-); also elsewhere on the board
unnamed 62: J4#2.A6 (D+), J4#2.B6 (D+); also elsewhere on the board
